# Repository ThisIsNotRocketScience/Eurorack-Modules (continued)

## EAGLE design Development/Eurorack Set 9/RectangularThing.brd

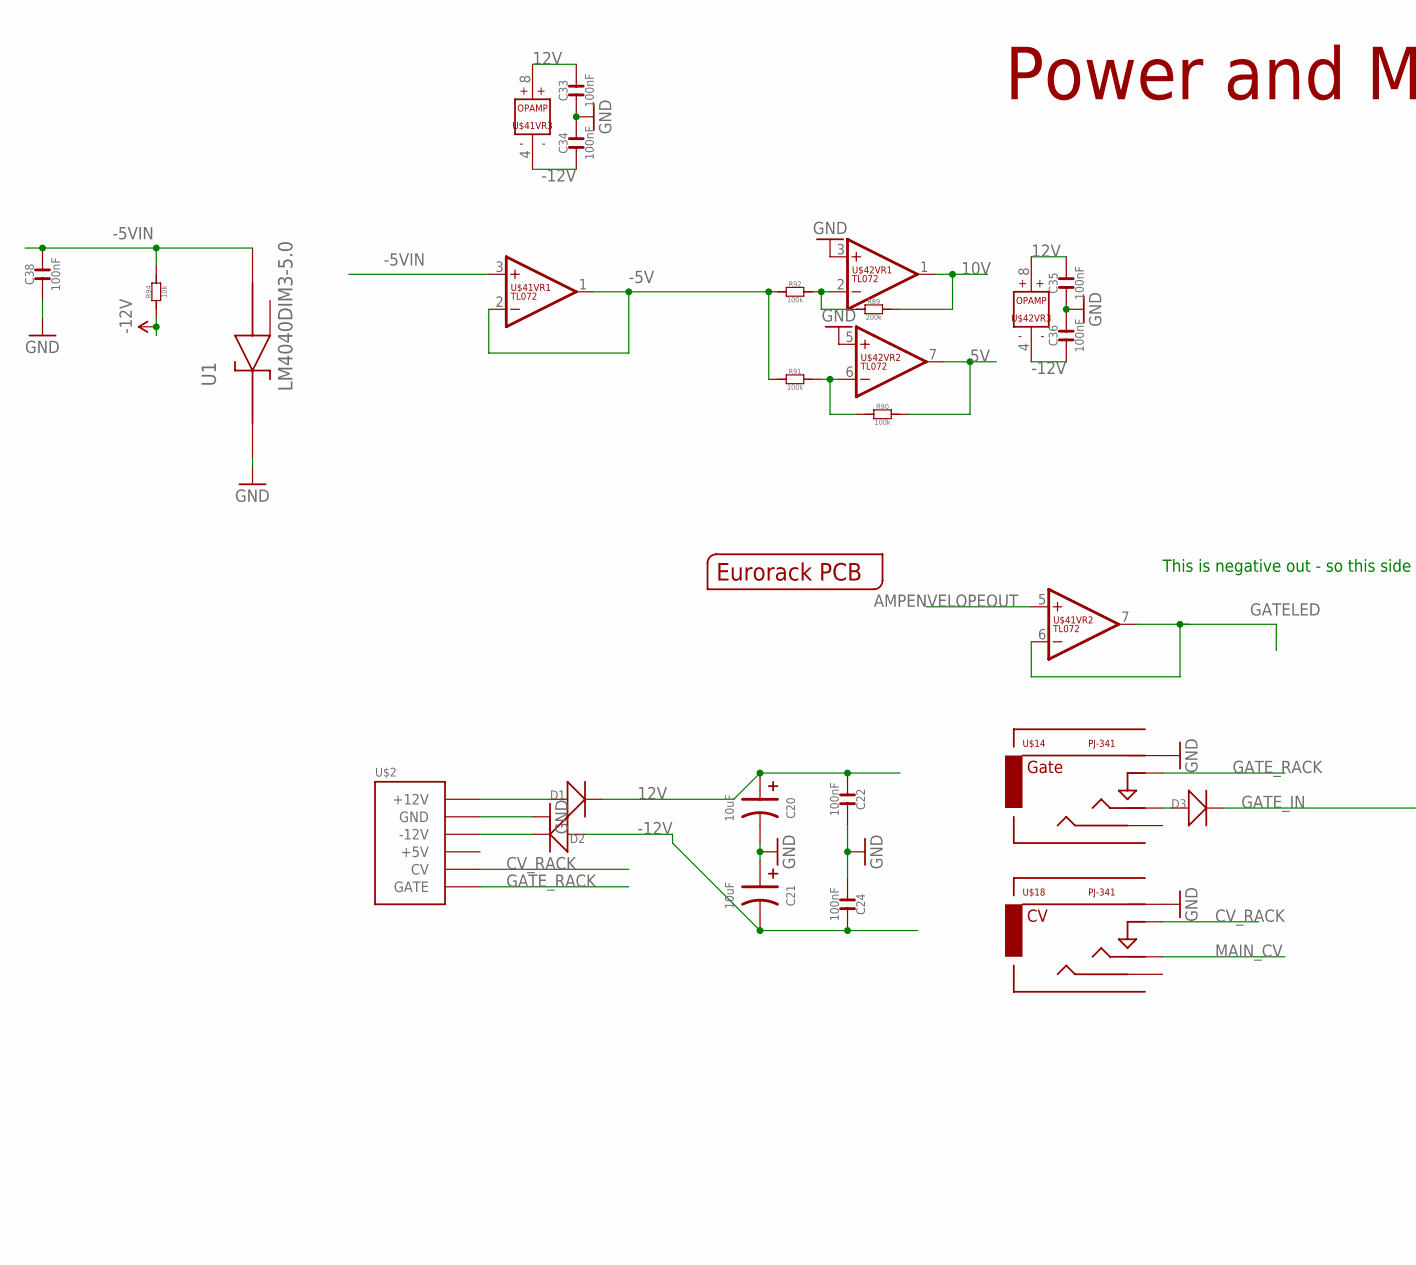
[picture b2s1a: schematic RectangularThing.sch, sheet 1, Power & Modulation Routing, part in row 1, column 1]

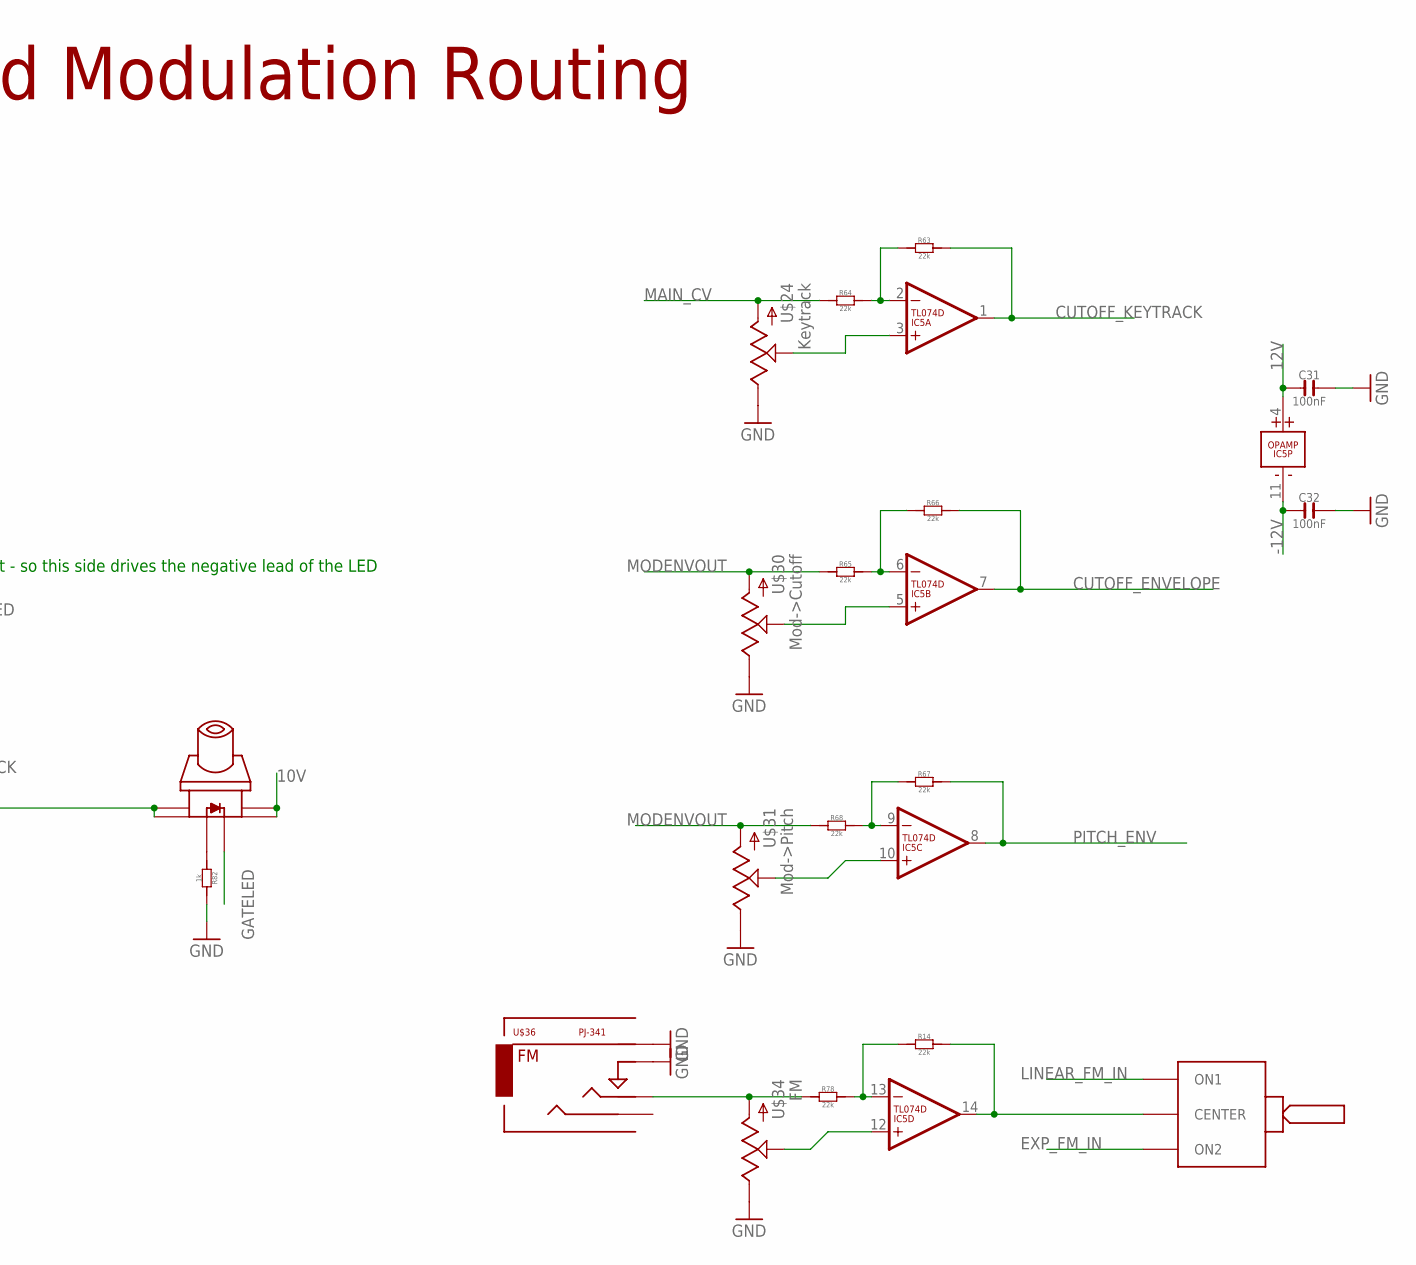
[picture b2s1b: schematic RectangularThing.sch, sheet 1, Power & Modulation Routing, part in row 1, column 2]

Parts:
C20, C21: 10uF; AVX-A
C22, C24, C31, C32, C33, C34, C35, C36: 100nF; C0603
C38: 100nF; C0603; MPN 06035C104KAT2A
D1, D2, D3: D-SMA; DO-214AC
IC5: TL074D; SO14
R14, R63, R64, R65, R66, R67, R68, R78: 22k; R0603
R82: 1k; R0603
R89: 200k; R0603
R90, R91, R92: 100k; R0603
R94: 10k; R0603
U1: LM4040DIM3-5.0; SOT95P237X112-3N
U$1: EURORACK_PCB20HP_10X10CM; EURORACK20HP_10X10CM
U$2: POWERSHROUDED; POWER_16_SHROUDED
U$14, U$18, U$36: PJ-341; 3.5MM-JACK-SWITCH-13MM-INPUT
U$24, U$30, U$31, U$34: POTZEPHPOT; OG-POTS_ALPS_POT_VERTICAL
U$35: ONOFFON; MULTICOMP1MS-ONOFFON
U$39: SWITCH_W_LED_PB6149L-X-102YELLOW; PB6149L
U$41, U$42: TL072; SO08

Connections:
5V: R90.2, U$42.7 (OUT); also elsewhere on the board
10V: R89.2, U$39.3, U$39.4, U$42.1 (OUT); also elsewhere on the board
12V: C20.+ (1), C22.1, C31.1, C33.2, C35.2, D1.2 (-), IC5.4 (V+), U$41.8 (V+), U$42.8 (V+); also elsewhere on the board
-5V: R91.1, R92.1, U$41.1 (OUT), U$41.2 (-IN); also elsewhere on the board
-5VIN: C38.2, R94.2, U1.2 (ANODE), U$41.3 (+IN)
-12V: C21.- (2), C24.2, C32.1, C34.1, C36.1, D2.1 (+), IC5.11 (V-), R94.1, U$41.4 (V-), U$42.4 (V-); also elsewhere on the board
AMPENVELOPEOUT: U$41.5 (+IN); also elsewhere on the board
CUTOFF_ENVELOPE: IC5.7 (OUT), R66.2; also elsewhere on the board
CUTOFF_KEYTRACK: IC5.1 (OUT), R63.2; also elsewhere on the board
CV_RACK: U$2.13 (CV), U$2.14 (CV), U$18.SWITCH@3 (SWITCH)
EXP_FM_IN: U$35.3 (ON2); also elsewhere on the board
GATELED: U$39.LEDNEG (NEG), U$41.6 (-IN), U$41.7 (OUT)
GATE_IN: D3.2 (-), U$39.1, U$39.2; also elsewhere on the board
GATE_RACK: U$2.15 (GATE), U$2.16 (GATE), U$14.SWITCH@3 (SWITCH)
GND: C20.- (2), C21.+ (1), C22.2, C24.1, C31.2, C32.2, C33.1, C34.2, C35.1, C36.2, C38.1, R82.2, U1.1 (CATHODE), U$2.3 (GND), U$2.4 (GND), U$2.5 (GND), U$2.6 (GND), U$2.7 (GND), U$2.8 (GND), U$14.RING@3 (RING), U$18.RING@3 (RING), U$24.P$1 (E), U$30.P$1 (E), U$31.P$1 (E), U$34.P$1 (E), U$36.RING@3 (RING), U$36.SWITCH@3 (SWITCH), U$42.3 (+IN), U$42.5 (+IN); also elsewhere on the board
LINEAR_FM_IN: U$35.1 (ON1); also elsewhere on the board
MAIN_CV: R64.1, U$18.TIP@3 (TIP), U$24.P$3 (A); also elsewhere on the board
MODENVOUT: R65.1, R68.1, U$30.P$3 (A), U$31.P$3 (A); also elsewhere on the board
unnamed: D1.1 (+), U$2.9 (+12V), U$2.10 (+12V)
unnamed: D2.2 (-), U$2.1 (-12V), U$2.2 (-12V)
unnamed: IC5.14 (OUT), R14.2, U$35.2 (CENTER)
unnamed: IC5.13 (-IN), R14.1, R78.2
unnamed: IC5.2 (-IN), R63.1, R64.2
unnamed: IC5.3 (+IN), U$24.P$2 (S)
unnamed: IC5.6 (-IN), R65.2, R66.1
unnamed: IC5.9 (-IN), R67.1, R68.2
unnamed: IC5.5 (+IN), U$30.P$2 (S)
unnamed: IC5.10 (+IN), U$31.P$2 (S)
unnamed: IC5.12 (+IN), U$34.P$2 (S)
unnamed: R78.1, U$34.P$3 (A), U$36.TIP@3 (TIP)
unnamed: D3.1 (+), U$14.TIP@3 (TIP)
unnamed: R82.1, U$39.LEDPOS (POS)
unnamed: R89.1, R92.2, U$42.2 (-IN)
unnamed: R90.1, R91.2, U$42.6 (-IN)
PITCH_ENV: IC5.8 (OUT), R67.2; also elsewhere on the board

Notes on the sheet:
This is negative out - so this side drives the negative lead of the LED
Power and Modulation Routing

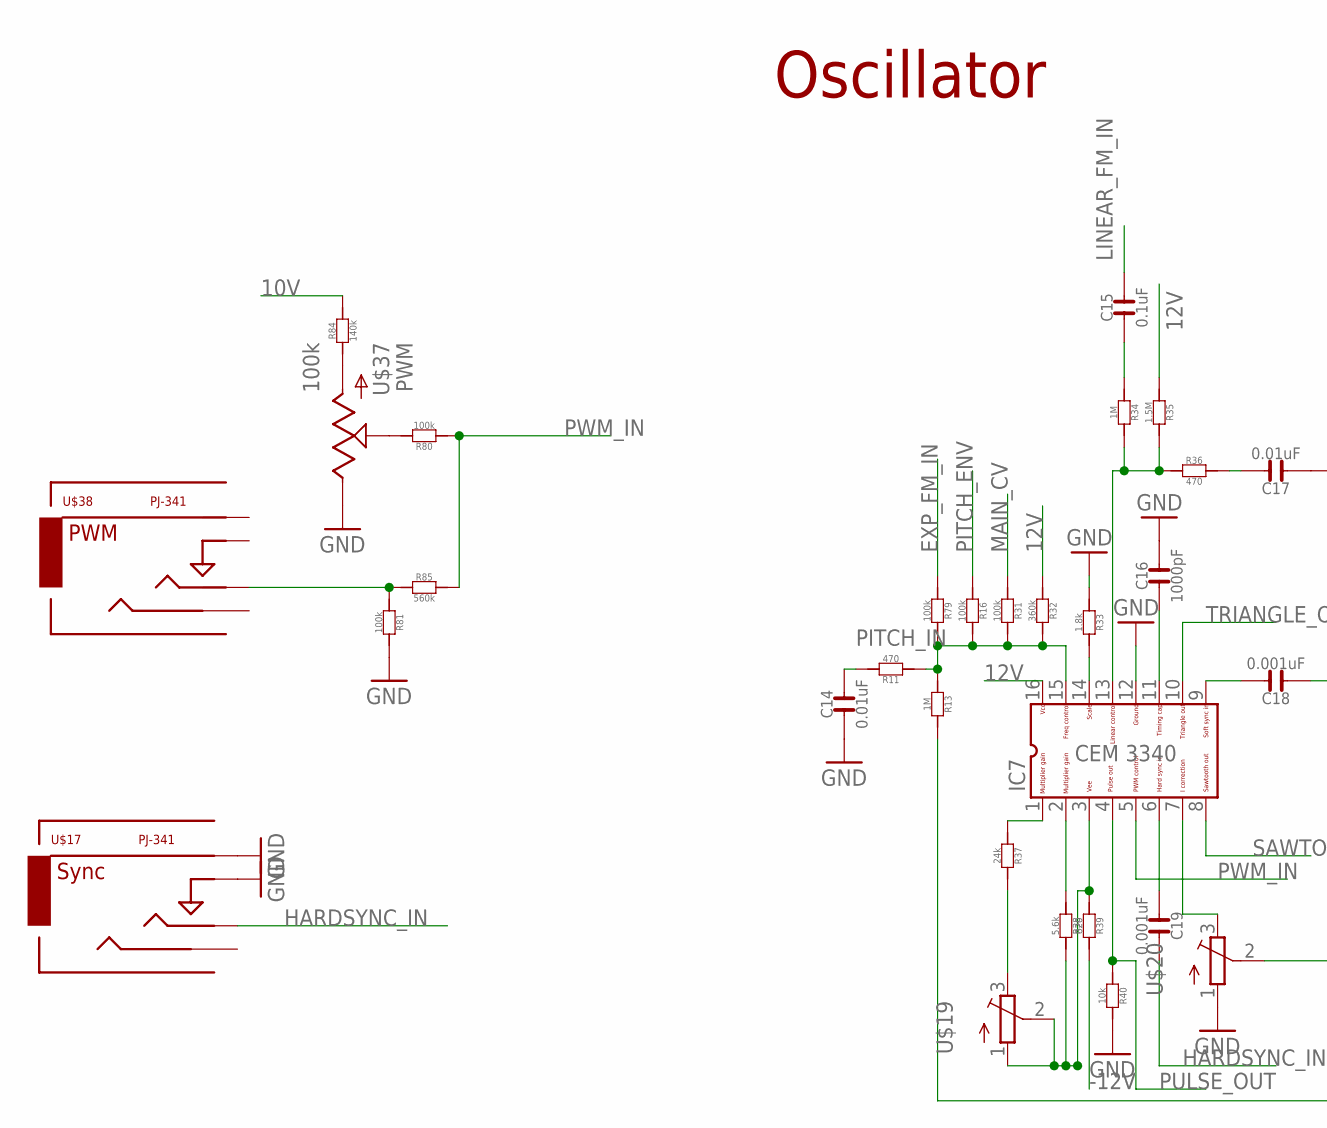
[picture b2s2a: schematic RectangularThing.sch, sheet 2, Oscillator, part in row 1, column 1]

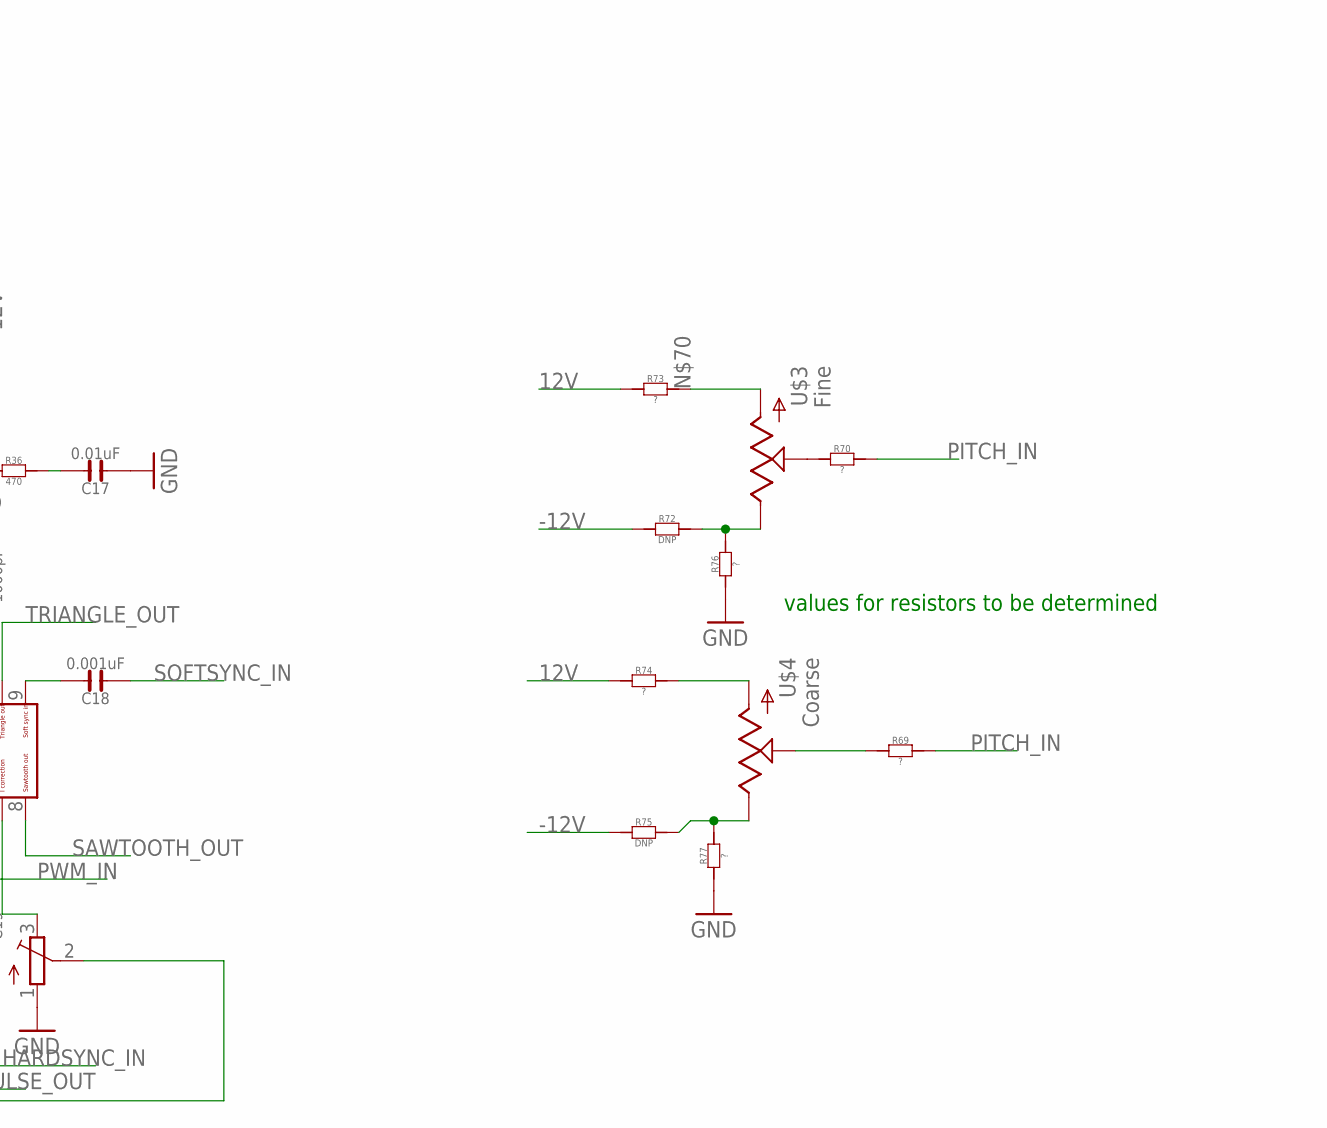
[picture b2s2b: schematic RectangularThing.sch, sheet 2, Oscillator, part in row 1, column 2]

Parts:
C14, C17: 0.01uF; C0603
C15: 0.1uF; C0603
C16: 1000pF; C0603
C18, C19: 0.001uF; C0603
IC7: CEM3340; DIL16
R11, R36: 470; R0603
R13, R34: 1M; R0603
R16, R31, R79, R80, R81: 100k; R0603
R32: 360k; R0603
R33: 1.8k; R0603
R35: 1.5M; R0603
R37: 24k; R0603
R38: 5.6k; R0603
R39: 820; R0603
R40: 10k; R0603
R69, R70, R73, R74, R76, R77: ?; R0603
R72, R75: DNP; R0603
R84: 140k; R0603
R85: 560k; R0603
U$3, U$4: POTZEPHPOT; OG-POTS_ALPS_POT_VERTICAL
U$17, U$38: PJ-341; 3.5MM-JACK-SWITCH-13MM-INPUT
U$19, U$20: TRIMPOTTC33X; TC33X
U$37: 100k; OG-POTS_ALPS_POT_VERTICAL

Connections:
10V: R84.2; also elsewhere on the board
12V: IC7.16, R32.1, R35.1, R73.1, R74.1; also elsewhere on the board
-12V: R39.2, R72.1, R75.1; also elsewhere on the board
EXP_FM_IN: R79.1; also elsewhere on the board
GND: C14.1, C16.2, C17.1, IC7.12, R33.1, R40.2, R76.1, R77.1, R81.2, U$17.RING@3 (RING), U$17.SWITCH@3 (SWITCH), U$20.1 (A), U$37.P$1 (E); also elsewhere on the board
HARDSYNC_IN: C19.2, U$17.TIP@3 (TIP)
LINEAR_FM_IN: C15.2; also elsewhere on the board
MAIN_CV: R31.1; also elsewhere on the board
unnamed: C14.2, R11.2
unnamed: C17.2, R36.2
unnamed: IC7.13, R34.2, R35.2, R36.1
unnamed: C15.1, R34.1
unnamed: C16.1, IC7.11
unnamed: C18.2, IC7.9
unnamed: IC7.14, R33.2
unnamed: C19.1, IC7.6
unnamed: IC7.1, R37.1
unnamed: R37.2, U$19.3 (E)
unnamed: IC7.3, R38.2, R39.1, U$19.1 (A), U$19.2 (S)
unnamed: R13.2, U$20.2 (S)
unnamed: IC7.2, R38.1
unnamed: IC7.7, U$20.3 (E)
unnamed: R73.2, U$3.P$3 (A)
unnamed: R72.2, R76.2, U$3.P$1 (E)
unnamed: R74.2, U$4.P$3 (A)
unnamed: R75.2, R77.2, U$4.P$1 (E)
unnamed: R69.1, U$4.P$2 (S)
unnamed: R70.1, U$3.P$2 (S)
unnamed: R80.2, U$37.P$2 (S)
unnamed: R84.1, U$37.P$3 (A)
unnamed: R81.1, R85.1, U$38.TIP@3 (TIP)
PITCH_ENV: R16.1; also elsewhere on the board
PITCH_IN: IC7.15, R11.1, R13.1, R16.2, R31.2, R32.2, R69.2, R70.2, R79.2
PULSE_OUT: IC7.4, R40.1; also elsewhere on the board
PWM_IN: IC7.5, R80.1, R85.2
SAWTOOTH_OUT: IC7.8; also elsewhere on the board
SOFTSYNC_IN: C18.1
TRIANGLE_OUT: IC7.10; also elsewhere on the board

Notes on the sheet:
Oscillator
values for resistors to be determined

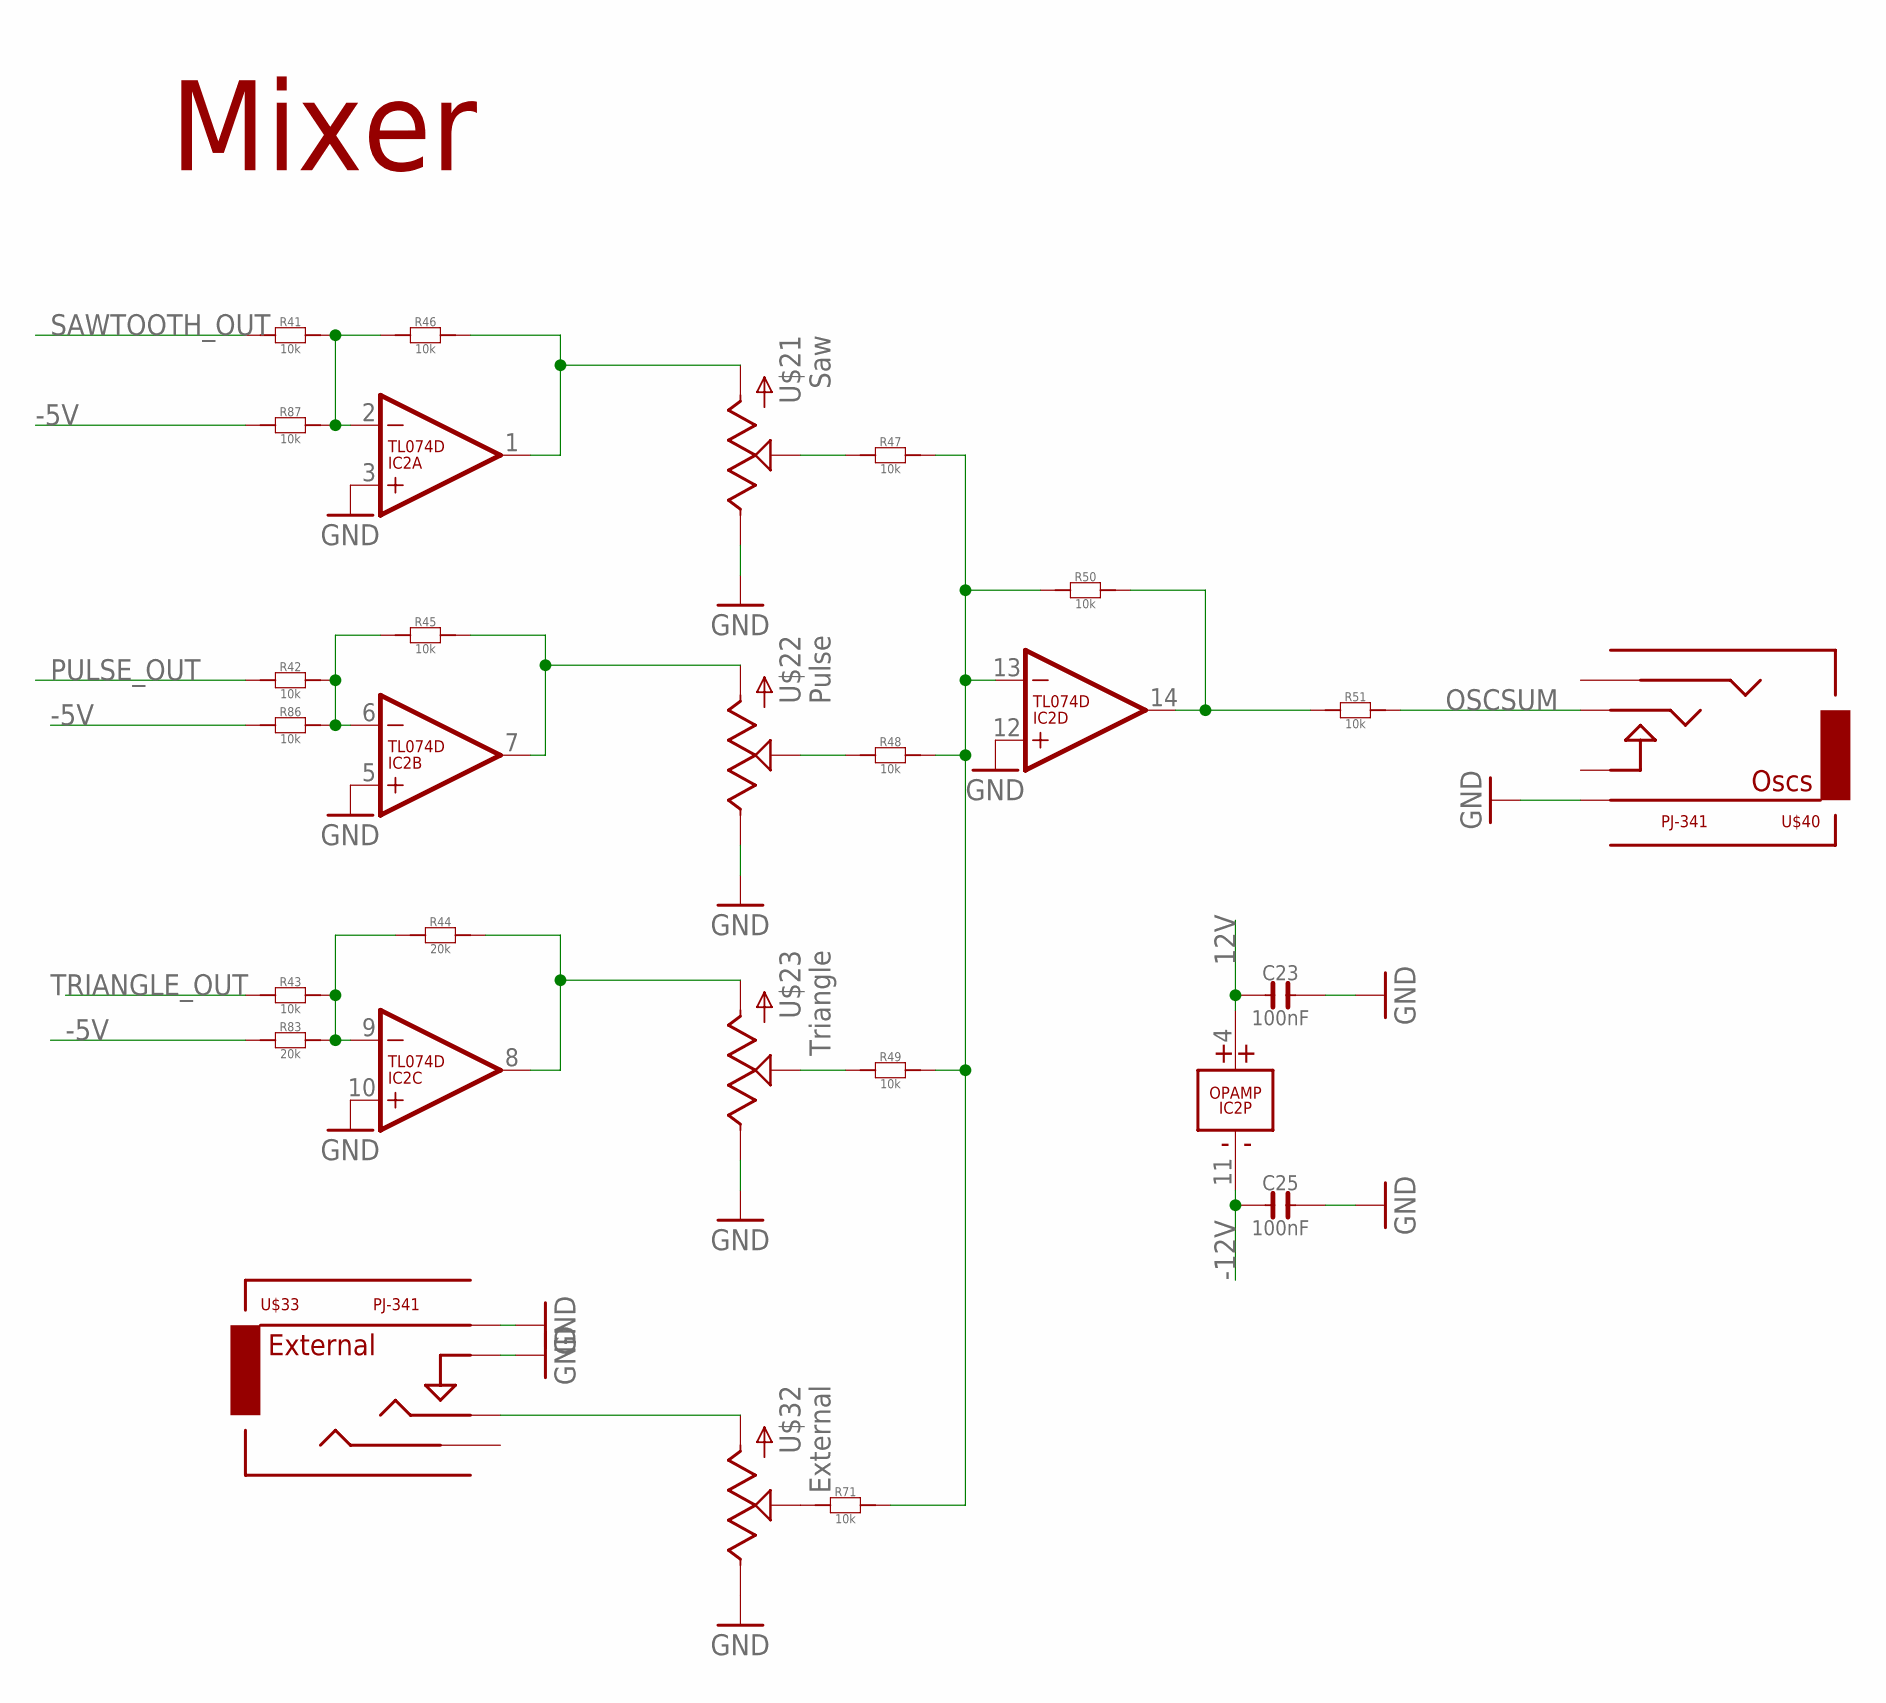
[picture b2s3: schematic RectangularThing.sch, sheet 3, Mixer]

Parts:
C23, C25: 100nF; C0603
IC2: TL074D; SO14
R41, R42, R43, R45, R46, R47, R48, R49, R50, R51, R71, R86, R87: 10k; R0603
R44, R83: 20k; R0603
U$21, U$22, U$23, U$32: POTZEPHPOT; OG-POTS_ALPS_POT_VERTICAL
U$33: PJ-341; 3.5MM-JACK-SWITCH-13MM-INPUT
U$40: PJ-341; 3.5MM-JACK-SWITCH-13MM-OUTPUT

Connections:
12V: C23.1, IC2.4 (V+); also elsewhere on the board
-5V: R83.1, R86.1, R87.1; also elsewhere on the board
-12V: C25.1, IC2.11 (V-); also elsewhere on the board
GND: C23.2, C25.2, IC2.3 (+IN), IC2.5 (+IN), IC2.10 (+IN), IC2.12 (+IN), U$21.P$1 (E), U$22.P$1 (E), U$23.P$1 (E), U$32.P$1 (E), U$33.RING@3 (RING), U$33.SWITCH@3 (SWITCH), U$40.RING@3 (RING); also elsewhere on the board
unnamed: IC2.14 (OUT), R50.2, R51.1
unnamed: IC2.13 (-IN), R47.2, R48.2, R49.2, R50.1, R71.2
unnamed: R49.1, U$23.P$2 (S)
unnamed: R48.1, U$22.P$2 (S)
unnamed: R47.1, U$21.P$2 (S)
unnamed: IC2.1 (OUT), R46.2, U$21.P$3 (A)
unnamed: IC2.7 (OUT), R45.2, U$22.P$3 (A)
unnamed: IC2.6 (-IN), R42.2, R45.1, R86.2
unnamed: IC2.2 (-IN), R41.2, R46.1, R87.2
unnamed: IC2.9 (-IN), R43.2, R44.1, R83.2
unnamed: IC2.8 (OUT), R44.2, U$23.P$3 (A)
unnamed: R71.1, U$32.P$2 (S)
unnamed: U$32.P$3 (A), U$33.TIP@3 (TIP)
OSCSUM: R51.2, U$40.TIP@3 (TIP); also elsewhere on the board
PULSE_OUT: R42.1; also elsewhere on the board
SAWTOOTH_OUT: R41.1; also elsewhere on the board
TRIANGLE_OUT: R43.1; also elsewhere on the board

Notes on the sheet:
Mixer

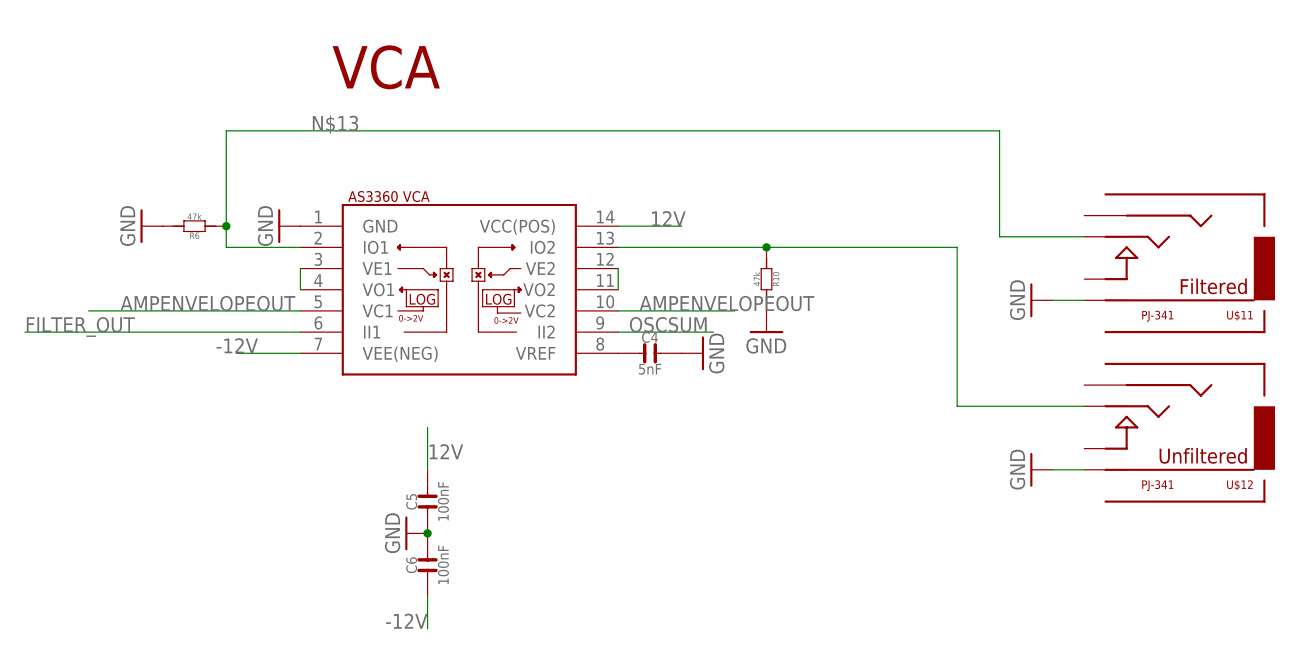
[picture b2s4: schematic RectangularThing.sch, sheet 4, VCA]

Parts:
C4: 5nF; C0603
C5, C6: 100nF; C0603
R6, R10: 47k; R0603
U$11, U$12: PJ-341; 3.5MM-JACK-SWITCH-13MM-OUTPUT
U$15: CEM3360; DIL14

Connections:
12V: C5.2, U$15.14 (VCC(POS)); also elsewhere on the board
-12V: C6.1, U$15.7 (VEE(NEG)); also elsewhere on the board
AMPENVELOPEOUT: U$15.5 (VC1), U$15.10 (VC2); also elsewhere on the board
FILTER_OUT: U$15.6 (II1); also elsewhere on the board
GND: C4.2, C5.1, C6.2, R6.2, R10.2, U$11.RING@3 (RING), U$12.RING@3 (RING), U$15.1 (GND); also elsewhere on the board
unnamed: C4.1, U$15.8 (VREF)
unnamed: U$15.3 (VE1), U$15.4 (VO1)
unnamed: R6.1, U$11.TIP@3 (TIP), U$15.2 (IO1)
unnamed: R10.1, U$12.TIP@3 (TIP), U$15.13 (IO2)
unnamed: U$15.11 (VO2), U$15.12 (VE2)
OSCSUM: U$15.9 (II2); also elsewhere on the board

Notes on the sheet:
VCA

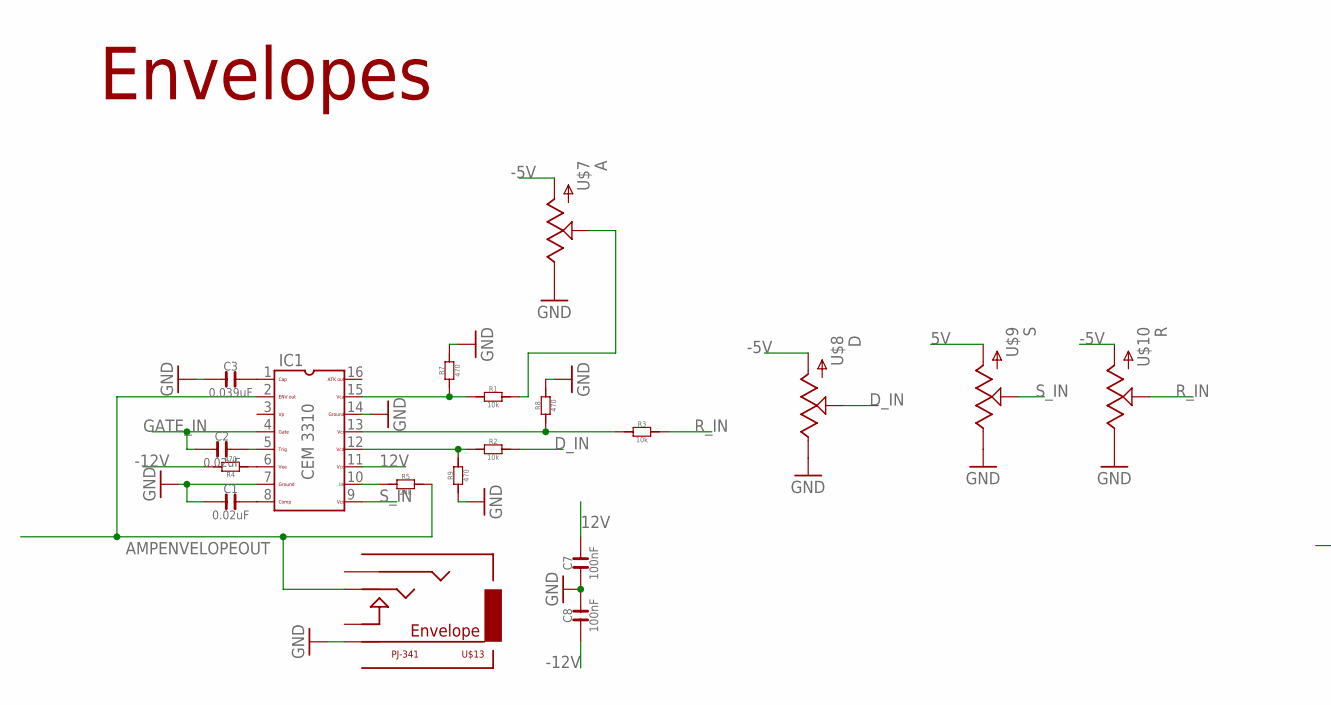
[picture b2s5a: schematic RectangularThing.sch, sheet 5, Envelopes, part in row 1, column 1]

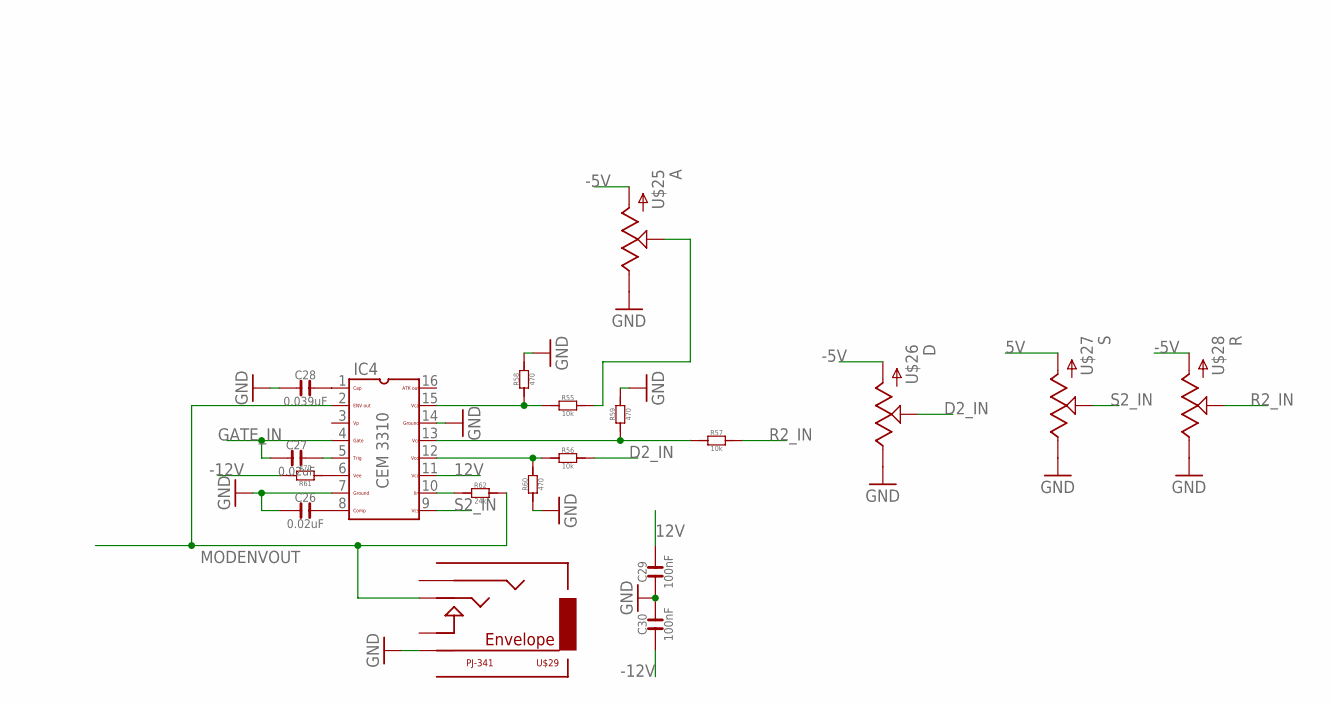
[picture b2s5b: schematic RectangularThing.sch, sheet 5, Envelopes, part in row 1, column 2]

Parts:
C1, C2, C26, C27: 0.02uF; C0603
C3, C28: 0.039uF; C0603
C7, C8, C29, C30: 100nF; C0603
IC1, IC4: CEM3310; DIL16
R1, R2, R3, R55, R56, R57: 10k; R0603
R4, R7, R8, R9, R58, R59, R60, R61: 470; R0603
R5, R62: 24k; R0603
U$7, U$8, U$9, U$10, U$25, U$26, U$27, U$28: POTZEPHPOT; OG-POTS_ALPS_POT_VERTICAL
U$13, U$29: PJ-341; 3.5MM-JACK-SWITCH-13MM-OUTPUT

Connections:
5V: U$9.P$3 (A), U$27.P$3 (A); also elsewhere on the board
12V: C7.2, C29.2, IC1.11, IC4.11; also elsewhere on the board
-5V: U$7.P$3 (A), U$8.P$3 (A), U$10.P$3 (A), U$25.P$3 (A), U$26.P$3 (A), U$28.P$3 (A); also elsewhere on the board
-12V: C8.1, C30.1, R4.2, R61.2; also elsewhere on the board
A2_IN: R55.2, U$25.P$2 (S)
AMPENVELOPEOUT: IC1.2, R5.2, U$13.TIP@3 (TIP); also elsewhere on the board
A_IN: R1.2, U$7.P$2 (S)
D2_IN: R56.2, U$26.P$2 (S)
D_IN: R2.2, U$8.P$2 (S)
GATE_IN: C2.1, C27.1, IC1.4, IC4.4; also elsewhere on the board
GND: C1.1, C3.1, C7.1, C8.2, C26.1, C28.1, C29.1, C30.2, IC1.7, IC1.14, IC4.7, IC4.14, R7.2, R8.2, R9.1, R58.2, R59.2, R60.1, U$7.P$1 (E), U$8.P$1 (E), U$9.P$1 (E), U$10.P$1 (E), U$13.RING@3 (RING), U$25.P$1 (E), U$26.P$1 (E), U$27.P$1 (E), U$28.P$1 (E), U$29.RING@3 (RING); also elsewhere on the board
MODENVOUT: IC4.2, R62.2, U$29.TIP@3 (TIP); also elsewhere on the board
unnamed: IC1.15, R1.1, R7.1
unnamed: IC1.12, R2.1, R9.2
unnamed: IC1.13, R3.1, R8.1
unnamed: C3.2, IC1.1
unnamed: C2.2, IC1.5
unnamed: IC1.6, R4.1
unnamed: C1.2, IC1.8
unnamed: IC1.10, R5.1
unnamed: IC4.15, R55.1, R58.1
unnamed: IC4.12, R56.1, R60.2
unnamed: IC4.13, R57.1, R59.1
unnamed: C27.2, IC4.5
unnamed: IC4.6, R61.1
unnamed: C26.2, IC4.8
unnamed: IC4.10, R62.1
unnamed: C28.2, IC4.1
R2_IN: R57.2, U$28.P$2 (S)
R_IN: R3.2, U$10.P$2 (S)
S2_IN: IC4.9, U$27.P$2 (S)
S_IN: IC1.9, U$9.P$2 (S)

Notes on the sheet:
Envelopes

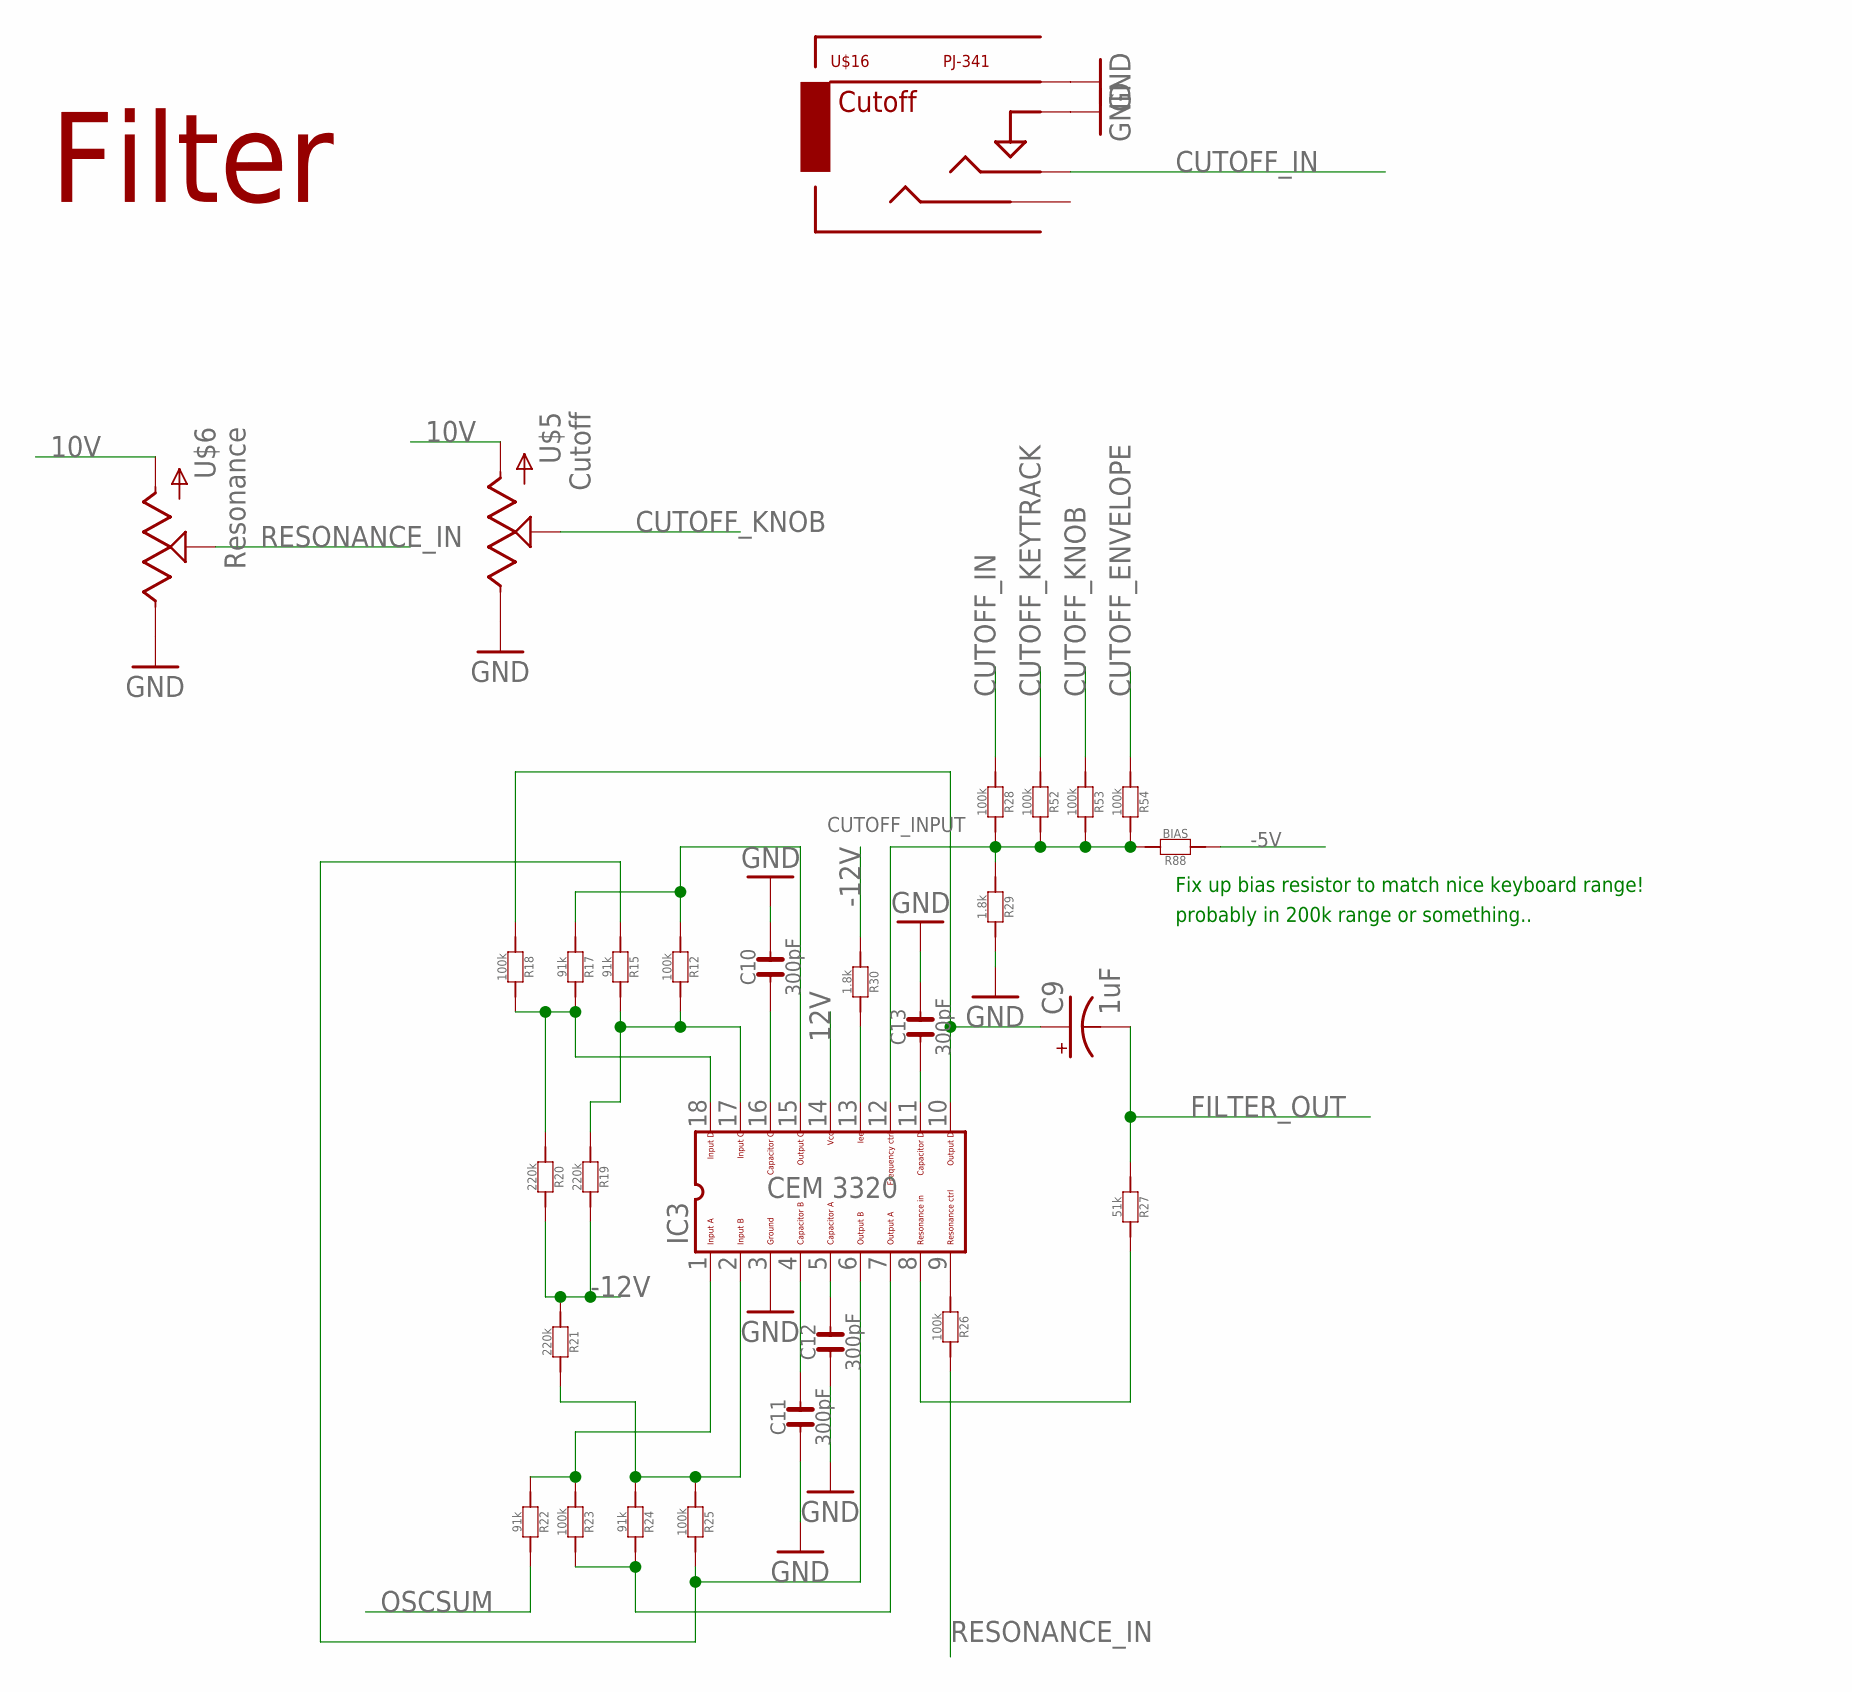
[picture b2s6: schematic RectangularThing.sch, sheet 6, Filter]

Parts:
C9: 1uF; 153CLV-0505
C10, C11, C12, C13: 300pF; C0603
IC3: CEM3320; DIL18
R12, R18, R23, R25, R26, R28, R52, R53, R54: 100k; R0603
R15, R17, R22, R24: 91k; R0603
R19, R20, R21: 220k; R0603
R27: 51k; R0603
R29, R30: 1.8k; R0603
R88: BIAS; R0603
U$5, U$6: POTZEPHPOT; OG-POTS_ALPS_POT_VERTICAL
U$16: PJ-341; 3.5MM-JACK-SWITCH-13MM-INPUT

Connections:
10V: U$5.P$3 (A), U$6.P$3 (A); also elsewhere on the board
12V: IC3.14; also elsewhere on the board
-5V: R88.1; also elsewhere on the board
-12V: R19.2, R20.2, R21.1, R30.1; also elsewhere on the board
CUTOFF_ENVELOPE: R54.1; also elsewhere on the board
CUTOFF_IN: R28.1, U$16.TIP@3 (TIP)
CUTOFF_INPUT: IC3.12, R28.2, R29.1, R52.2, R53.2, R54.2, R88.2
CUTOFF_KEYTRACK: R52.1; also elsewhere on the board
CUTOFF_KNOB: R53.1, U$5.P$2 (S)
FILTER_OUT: C9.-, R27.1; also elsewhere on the board
GND: C10.2, C11.1, C12.1, C13.2, IC3.3, R29.2, U$5.P$1 (E), U$6.P$1 (E), U$16.RING@3 (RING), U$16.SWITCH@3 (SWITCH); also elsewhere on the board
unnamed: C10.1, IC3.16
unnamed: C11.2, IC3.4
unnamed: C12.2, IC3.5
unnamed: C13.1, IC3.11
unnamed: IC3.9, R26.1
unnamed: IC3.1, R22.1, R23.1
unnamed: IC3.7, R23.2, R24.2
unnamed: IC3.6, R15.1, R25.2
unnamed: IC3.18, R17.2, R18.2, R20.1
unnamed: IC3.17, R12.2, R15.2, R19.1
unnamed: IC3.15, R12.1, R17.1
unnamed: IC3.13, R30.2
unnamed: C9.+, IC3.10, R18.1
unnamed: IC3.8, R27.2
unnamed: IC3.2, R21.2, R24.1, R25.1
OSCSUM: R22.2; also elsewhere on the board
RESONANCE_IN: R26.2, U$6.P$2 (S)

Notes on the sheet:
Filter
Fix up bias resistor to match nice keyboard range!
probably in 200k range or something..
